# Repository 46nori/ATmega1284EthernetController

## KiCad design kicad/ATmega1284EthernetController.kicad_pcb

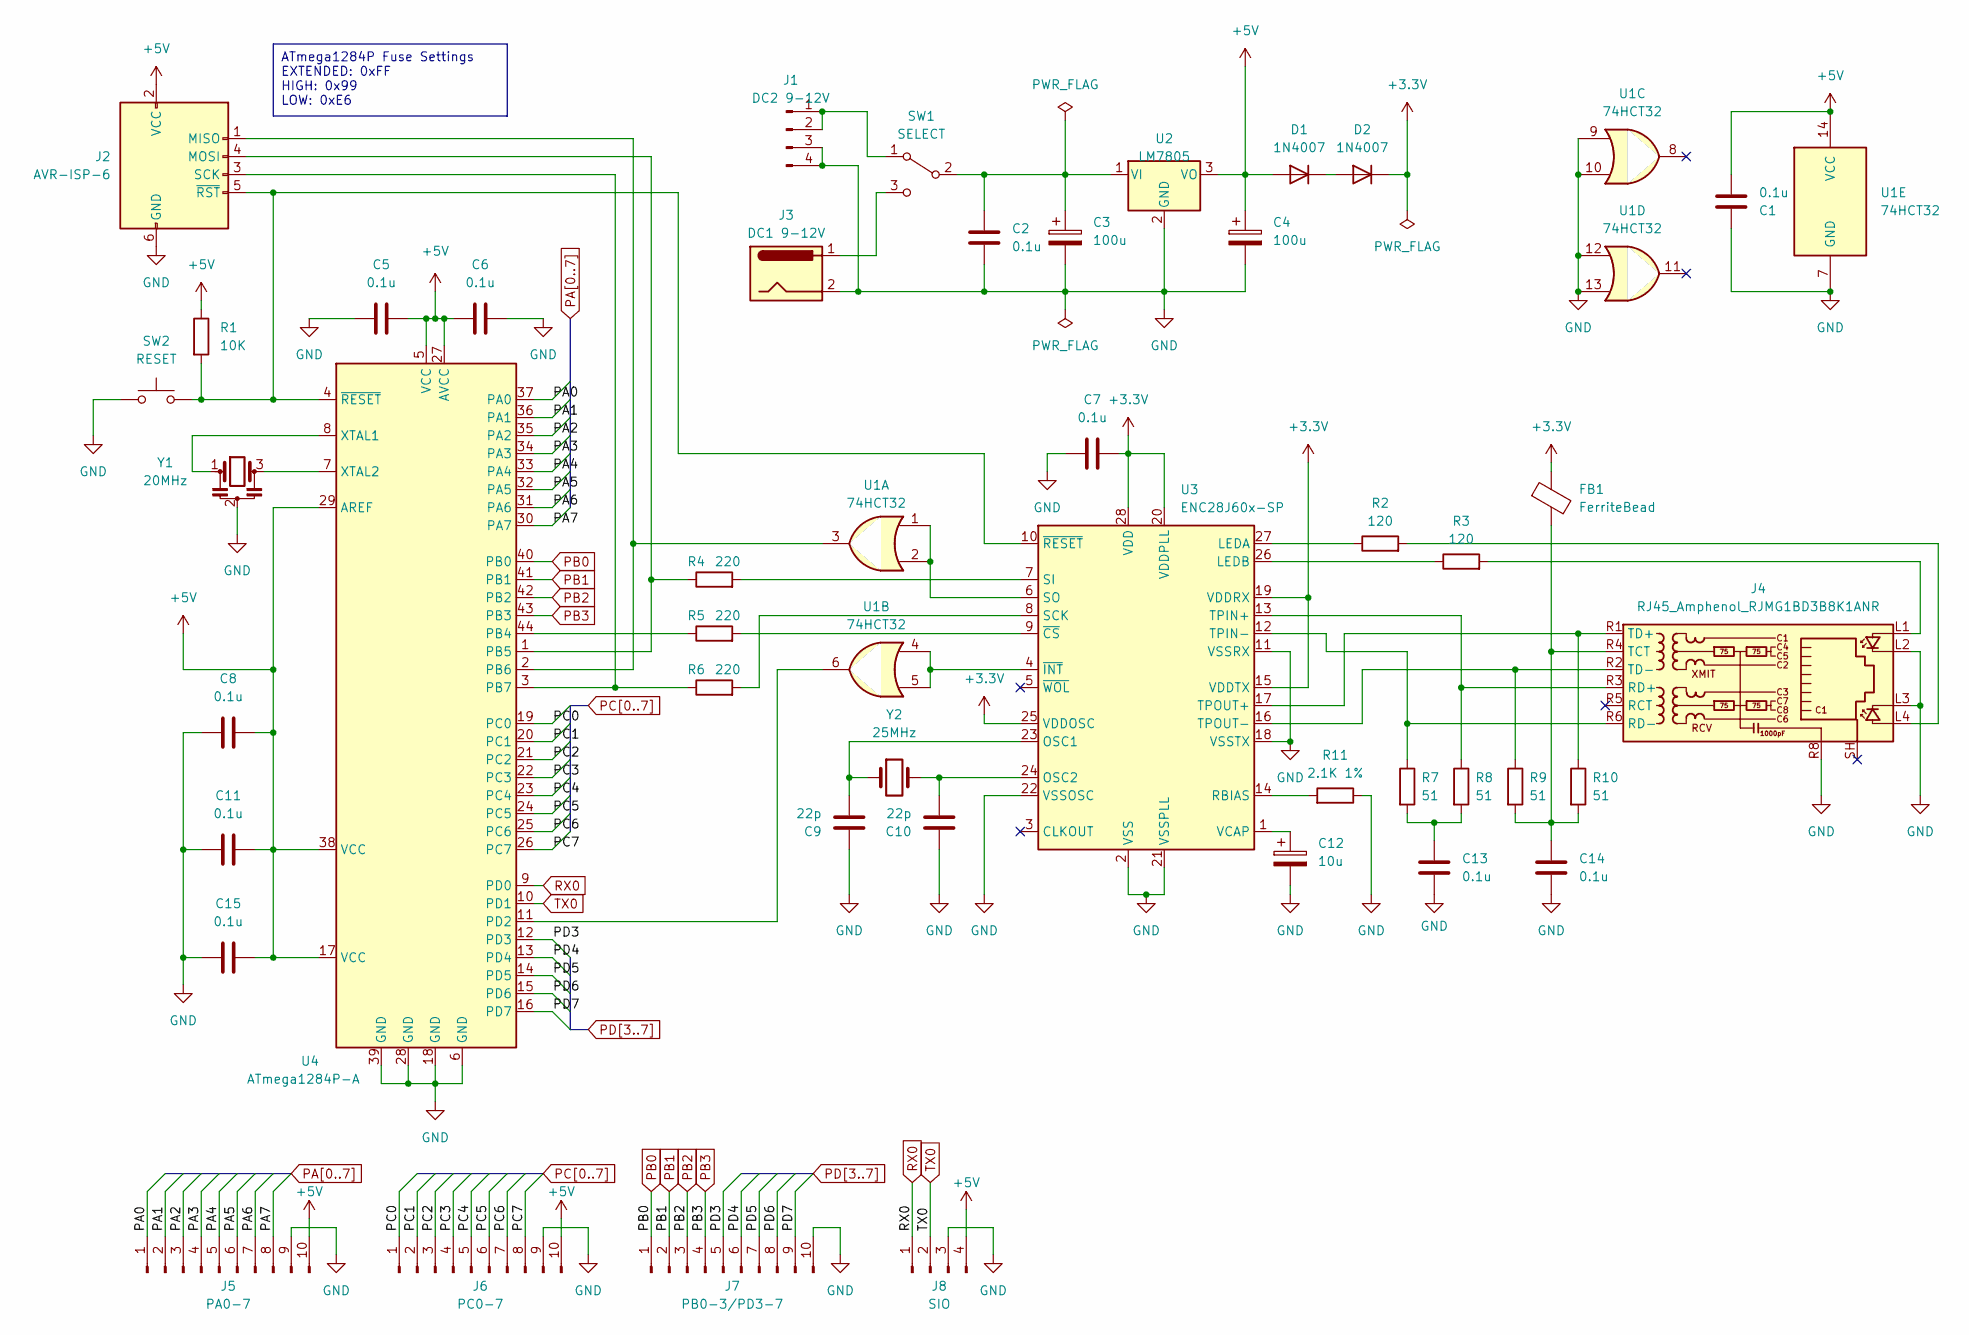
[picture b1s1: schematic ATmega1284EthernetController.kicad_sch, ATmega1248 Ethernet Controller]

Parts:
C1, C2, C5, C6, C7, C8, C11, C13, C14, C15: 0.1u; C_Disc_D3.8mm_W2.6mm_P2.50mm
C3, C4: 100u; CP_Radial_D5.0mm_P2.50mm
C9, C10: 22p; C_Disc_D3.8mm_W2.6mm_P2.50mm
C12: 10u; CP_Radial_D5.0mm_P2.50mm
D1, D2: 1N4007; D_DO-41_SOD81_P10.16mm_Horizontal
FB1: FerriteBead; LairdTech_28C0236-0JW-10
J1: DC2 9-12V; PinHeader_1x04_P2.00mm_Vertical
J2: AVR-ISP-6; PinHeader_2x03_P2.54mm_Vertical
J3: DC1 9-12V; BarrelJack_Horizontal
J4: RJ45_Amphenol_RJMG1BD3B8K1ANR
J5: PA0-7; PinHeader_1x10_P2.54mm_Vertical
J6: PC0-7; PinHeader_1x10_P2.54mm_Vertical
J7: PB0-3/PD3-7; PinHeader_1x10_P2.54mm_Vertical
J8: SIO; PinHeader_1x04_P2.54mm_Vertical
R1: 10K; R_Axial_DIN0207_L6.3mm_D2.5mm_P10.16mm_Horizontal
R2, R3: 120; R_Axial_DIN0207_L6.3mm_D2.5mm_P10.16mm_Horizontal
R4, R5, R6: 220; R_Axial_DIN0207_L6.3mm_D2.5mm_P10.16mm_Horizontal
R7, R8, R9, R10: 51; R_Axial_DIN0207_L6.3mm_D2.5mm_P10.16mm_Horizontal
R11: 2.1K 1%; R_Axial_DIN0207_L6.3mm_D2.5mm_P10.16mm_Horizontal
SW1: SELECT; SW_Slide_1P2T_CK_OS102011MS2Q
SW2: RESET; SW_PUSH_6mm_H7.3mm
U1: 74HCT32; DIP-14_W7.62mm_Socket
U2: LM7805; TO-220-3_Vertical
U3: ENC28J60x-SP; DIP-28_W7.62mm
U4: ATmega1284P-A; TQFP-44_10x10mm_P0.8mm
Y1: 20MHz; Resonator_Murata_CSTLSxxxX-3Pin_W5.5mm_H3.0mm
Y2: 25MHz; Crystal_HC18-U_Vertical

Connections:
+3.3V: C7.2, D2.1 (K), FB1.1, U3.15 (VDDTX), U3.19 (VDDRX), U3.20 (VDDPLL), U3.25 (VDDOSC), U3.28 (VDD)
+5V: C1.2, C4.1, C5.2, C6.1, C8.1, C11.2, C15.1, D1.2 (A), J2.2 (VCC), J5.10, J6.10, J8.4, R1.1, U1.14 (VCC), U2.3 (VO), U4.5 (VCC), U4.17 (VCC), U4.27 (AVCC), U4.29 (AREF), U4.38 (VCC)
GND: C1.1, C2.2, C3.2, C4.2, C5.1, C6.2, C7.1, C8.2, C9.1, C10.1, C11.1, C12.2, C13.2, C14.2, C15.2, J1.3, J1.4, J2.6 (GND), J3.2, J4.L2, J4.L3, J4.R8, J5.9, J6.9, J7.10, J8.3, R11.1, SW2.1, U1.7 (GND), U1.9, U1.10, U1.12, U1.13, U2.2 (GND), U3.2 (VSS), U3.11 (VSSRX), U3.18 (VSSTX), U3.21 (VSSPLL), U3.22 (VSSOSC), U4.6 (GND), U4.18 (GND), U4.28 (GND), U4.39 (GND), Y1.2
unnamed: C13.1, R7.2, R8.2
unnamed: D1.1 (K), D2.2 (A)
unnamed: J1.1, J1.2, SW1.1 (A)
unnamed: J2.1 (MISO), U1.3, U4.2 (PB6)
unnamed: J2.4 (MOSI), R4.1, U4.1 (PB5)
unnamed: J2.3 (SCK), R6.1, U4.3 (PB7)
unnamed: J2.5 (~RST), R1.2, SW2.2, U3.10 (~RESET), U4.4 (~RESET)
unnamed: J4.L1, R3.2
unnamed: J4.L4, R2.2
unnamed: J4.R3 (RD+), R8.1, U3.13 (TPIN+)
unnamed: J4.R6 (RD-), R7.1, U3.12 (TPIN-)
unnamed: C14.1, FB1.2, J4.R4 (TCT), R9.2, R10.2
unnamed: J4.R1 (TD+), R10.1, U3.17 (TPOUT+)
unnamed: J4.R2 (TD-), R9.1, U3.16 (TPOUT-)
unnamed: C2.1, C3.1, SW1.2 (B), U2.1 (VI)
unnamed: J3.1, SW1.3 (C)
unnamed: R2.1, U3.27 (LEDA)
unnamed: R3.1, U3.26 (LEDB)
unnamed: C9.2, U3.23 (OSC1), Y2.1
unnamed: C10.2, U3.24 (OSC2), Y2.2
unnamed: R11.2, U3.14 (RBIAS)
unnamed: R6.2, U3.8 (SCK)
unnamed: R4.2, U3.7 (SI)
unnamed: U1.1, U1.2, U3.6 (SO)
unnamed: C12.1, U3.1 (VCAP)
unnamed: R5.2, U3.9 (~CS)
unnamed: U1.4, U1.5, U3.4 (~INT)
unnamed: R5.1, U4.44 (PB4)
unnamed: U1.6, U4.11 (PD2)
unnamed: U4.8 (XTAL1), Y1.1
unnamed: U4.7 (XTAL2), Y1.3
PA0: J5.1, U4.37 (PA0)
PA1: J5.2, U4.36 (PA1)
PA2: J5.3, U4.35 (PA2)
PA3: J5.4, U4.34 (PA3)
PA4: J5.5, U4.33 (PA4)
PA5: J5.6, U4.32 (PA5)
PA6: J5.7, U4.31 (PA6)
PA7: J5.8, U4.30 (PA7)
PB0: J7.1, U4.40 (PB0)
PB1: J7.2, U4.41 (PB1)
PB2: J7.3, U4.42 (PB2)
PB3: J7.4, U4.43 (PB3)
PC0: J6.1, U4.19 (PC0)
PC1: J6.2, U4.20 (PC1)
PC2: J6.3, U4.21 (PC2)
PC3: J6.4, U4.22 (PC3)
PC4: J6.5, U4.23 (PC4)
PC5: J6.6, U4.24 (PC5)
PC6: J6.7, U4.25 (PC6)
PC7: J6.8, U4.26 (PC7)
PD3: J7.5, U4.12 (PD3)
PD4: J7.6, U4.13 (PD4)
PD5: J7.7, U4.14 (PD5)
PD6: J7.8, U4.15 (PD6)
PD7: J7.9, U4.16 (PD7)
RX0: J8.1, U4.9 (PD0)
TX0: J8.2, U4.10 (PD1)

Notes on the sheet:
ATmega1284P Fuse Settings EXTENDED: 0xFF HIGH: 0x99 LOW: 0xE6

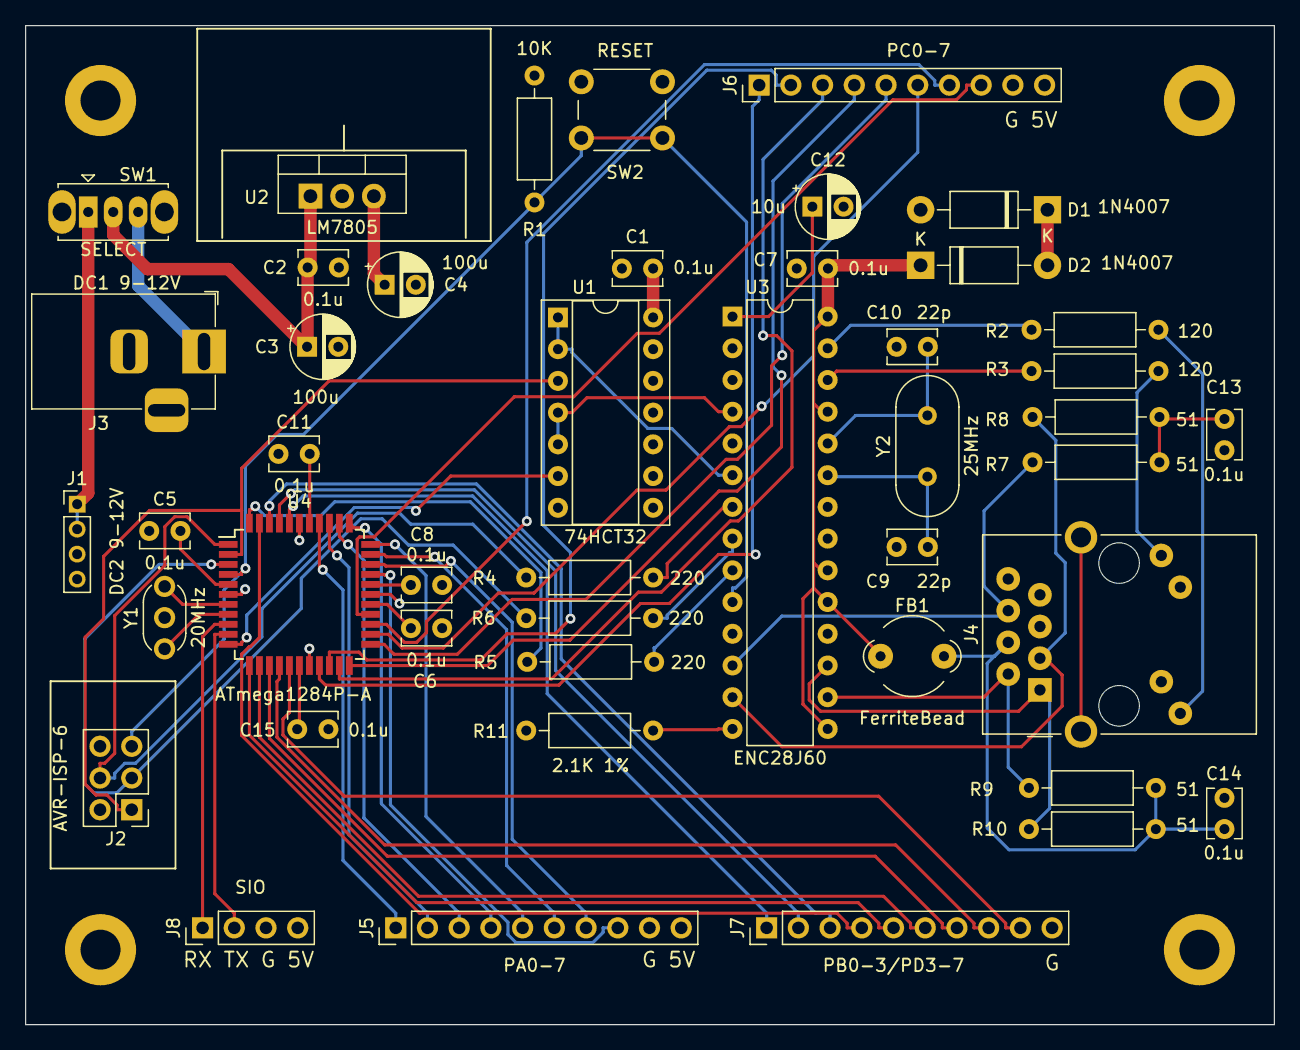
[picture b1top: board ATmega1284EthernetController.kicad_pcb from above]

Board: 4 copper layers, 100.0 x 80.0 mm, 45 parts (0 on the bottom side), 61 nets.

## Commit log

2023-12-29 Initial
2023-12-29 Changed footprint of AVR-ISP
2023-12-30 PCB base
2024-01-15 Added the origin point
